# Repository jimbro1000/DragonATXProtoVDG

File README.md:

# Dragon 32 ATX Prototype VDG

This repository contains the KiCad project files
to produce the VDG component board for my
ATX Prototype backplane.

This design requires the ATX backplane board in order 
to operate
See https://github.com/jimbro1000/DragonATXProto

## Notes

Revision 1 includes a more modern RGB fed modulator
design that removes a significant problem in the 
form of the old LM1889 modulator. The board also
provides the mounting points for the various mezzanine
boards that have been previously developed. If the
mezzanine option is to be used the rest of the card
should be left unpopulated

This design has been completed using KiCad 9. Earlier
versions of KiCad are not compatible

## Theory of Operation - Video conversion

The video output of the 6847 is a form of YPrPb that
encodes the green channel data over all three of the
outputs.

To generate the RGB signal required for the AD724/725
video encoder some maths needs to be applied to
convert the YPrPb into the appropriate format.

The maths requires 5 values to be generated

Yn - the inverse signal of Y
B-Y - the inverse of Pb
Y-B - Pb
R-Y - the inverse of Pr
Y-R - Pr

Adding Yn to R-Y produces R
Adding Yn to Y-R and Y-B produces G
Adding Yn to B-Y produces B

All of the sums need weighting to make sure the results
are in some form of balance:

R = 2Yn + 2.7(R-Y)
G = 2Yn + 6.8(Y-B) + 4.7(Y-R)
B = 3Yn + 2(R-Y)

Further provision for balancing the channels is made
through a potentiometer on each channel and the result
is then normalised to provide the inputs to the AD724

## Theory of Operation - Format conversion

The 6847 video generator was designed to produce a 
video signal in NTSC format. It has no external controls
to change the format, thus in order to produce a PAL
format some cheating is required in the form of padding

The native NTSC signal is produced at a 60Hz frame rate,
while PAL requires 50Hz. In proportion the PAL video
frame has extra lines (625 vs 525), this results in near
identical lines per second between the formats (but not 
quite identical, just within tolerance).

In terms of raw refresh rate though the PAL signal 
requires an additional 100 lines of video signal are 
produced. This is achieved by suspending the video clock
for the 6847 and synthesizing 50 lines of blank video in
the upper and lower margins of the display.

This is not the end of the story though - a more fundamental
difference between NTSC and PAL is how colour information
is encoded. NTSC provides no automatic correction for any
phase errors in the signal while PAL using phase alternation
(hence the name PAL). Producing a PAL signal from NTSC 
requires the colour phase to be reversed on each consecutive
line.

The original PAL padding circuitry this replaces used a
LM1889 encoder for encoding the colour signal onto the
carrier frequency but with the AD724 and AD725 encoders
this is performed automatically.

The circuit design retains the necessary logic for
artificially producing the alternating signal but does
not utilise it.

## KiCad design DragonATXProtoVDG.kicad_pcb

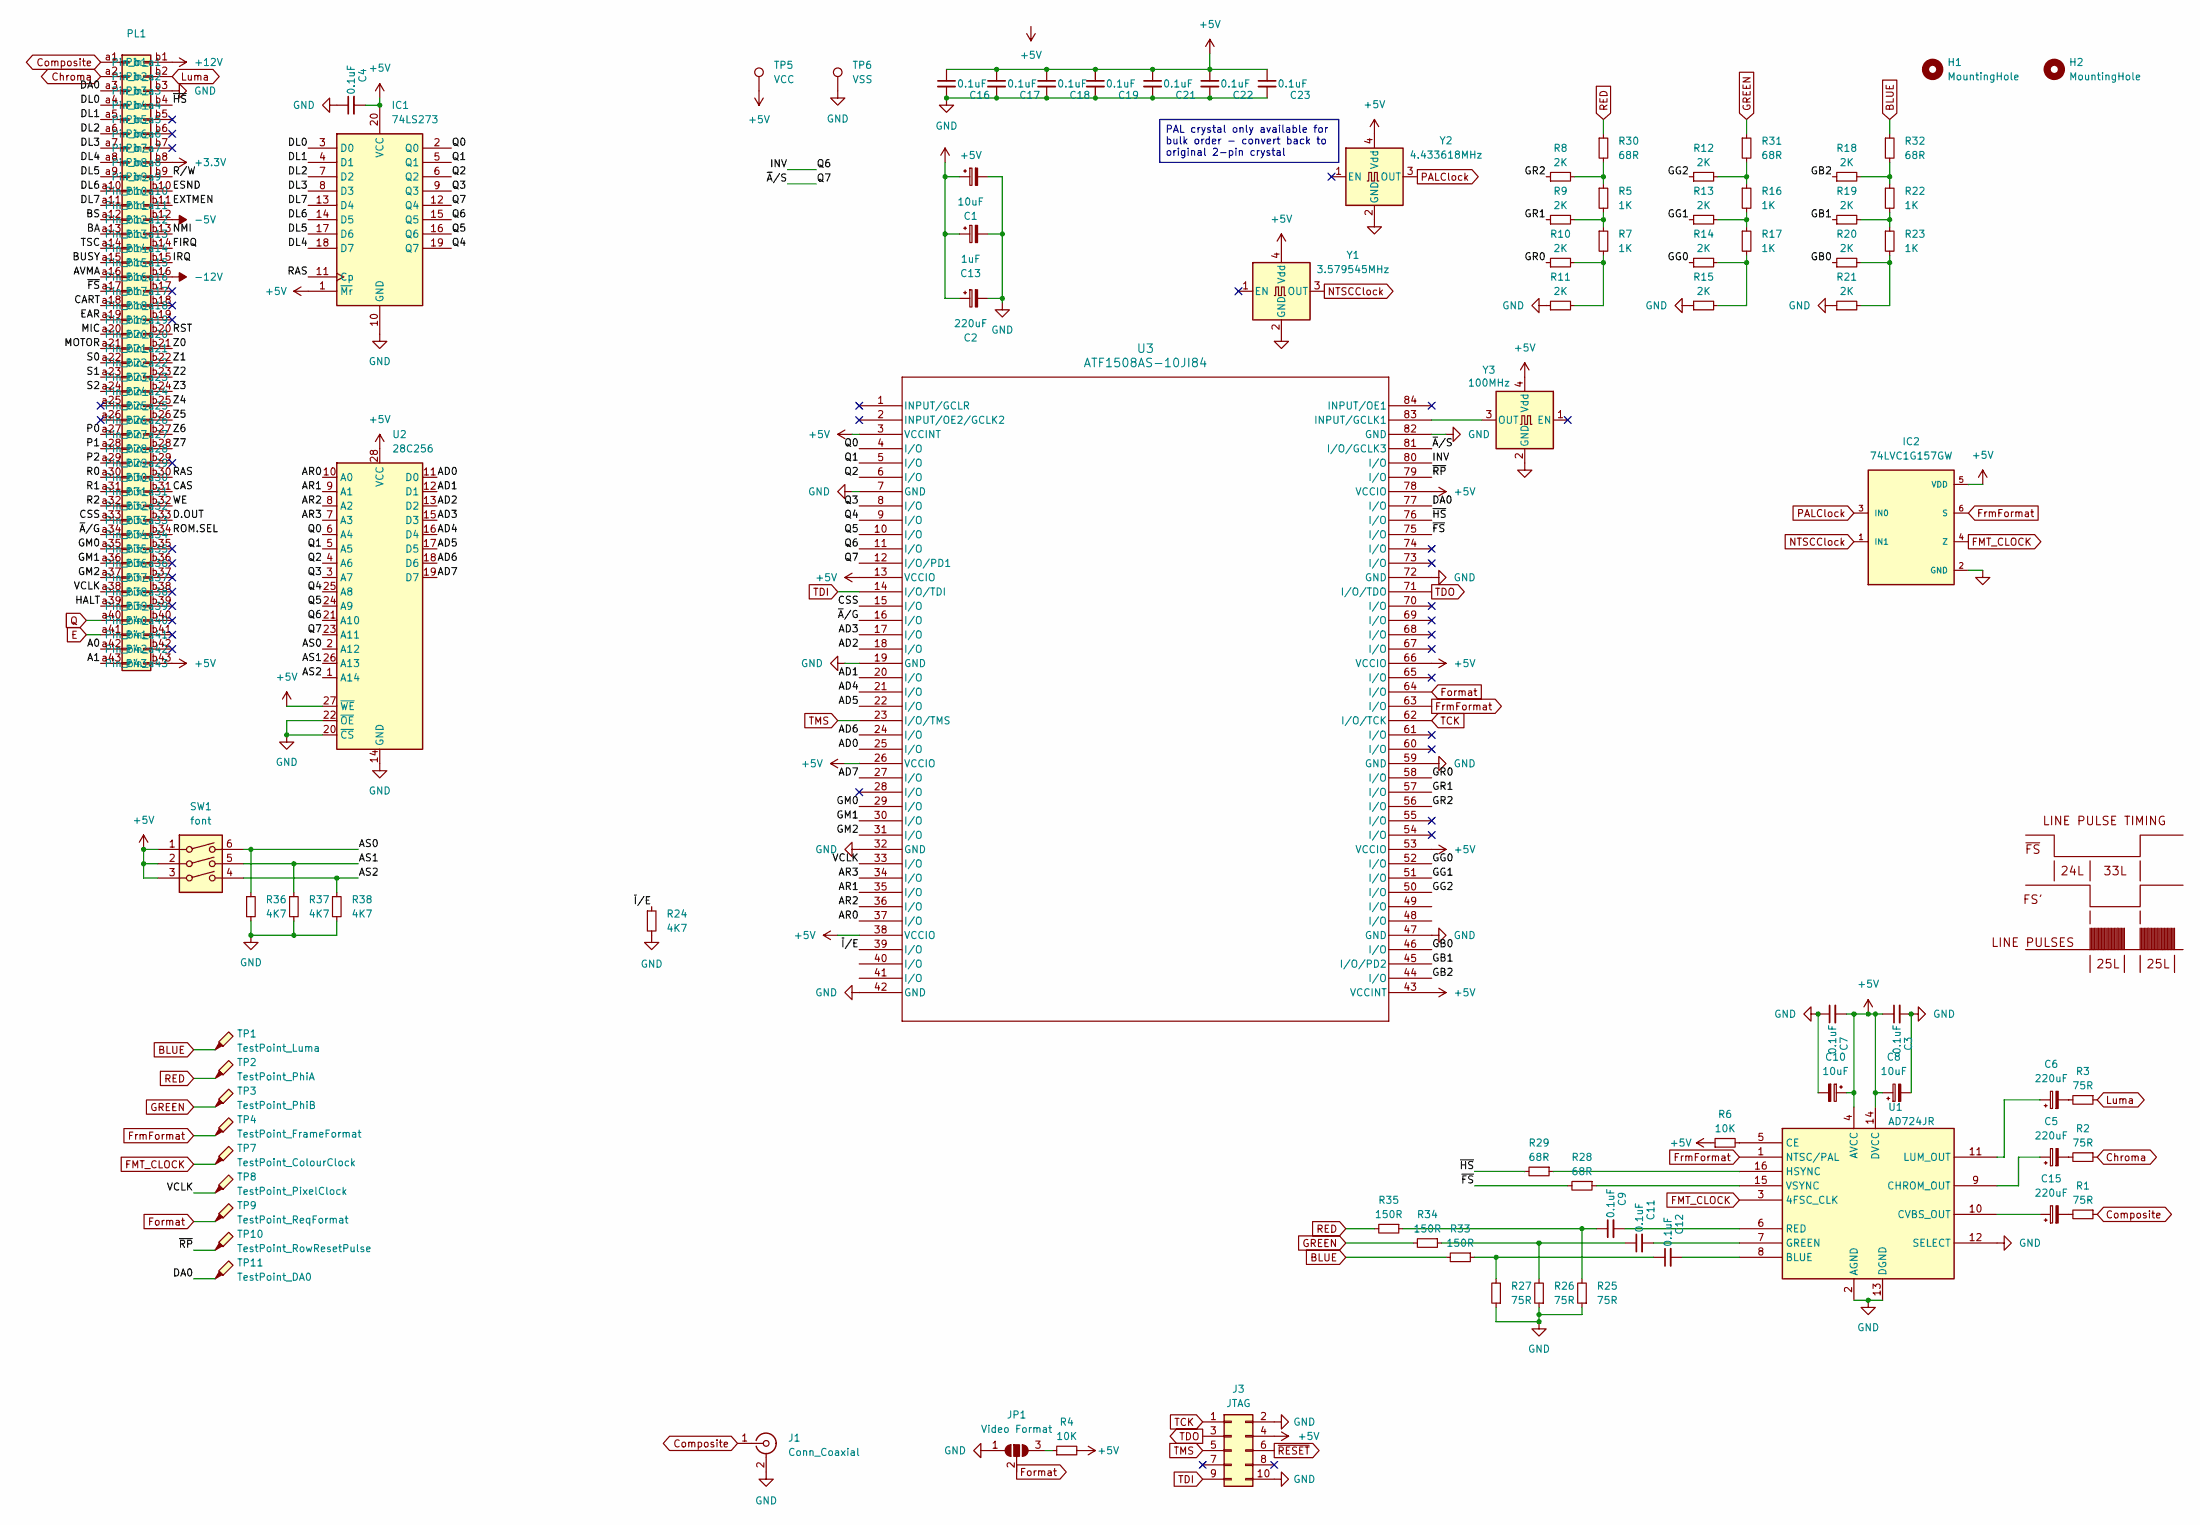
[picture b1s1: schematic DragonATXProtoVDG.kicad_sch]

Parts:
C1: 10uF; CP_Elec_4x5.4; DigiKey 732-8254-1-ND
C2: 220uF; CP_Elec_6.3x5.8; DigiKey 732-8254-1-ND
C3, C4, C7, C9, C11, C12, C16, C17, C18, C19, C21, C22, C23: 0.1uF; C_0805_2012Metric_Pad1.18x1.45mm_HandSolder; DigiKey 399-C0805C104M5RAC7800CT-ND
C5, C6, C15: 220uF; CP_EIA-6032-15_Kemet-U; DigiKey 478-1768-1-ND
C8, C10: 10uF; CP_Elec_4x5.4; DigiKey 732-6401-1-ND
C13: 1uF; CP_Elec_4x4.5; DigiKey 732-8541-1-ND
H1, H2: MountingHole; MountingHole_3.2mm_M3
IC1: 74LS273; SOIC-20W_7.5x12.8mm_P1.27mm; DigiKey 296-3682-1-ND
IC2: 74LVC1G157GW; SOT-363_SC-70-6_Handsoldering; DigiKey 1727-3491-1-ND
J1: Conn_Coaxial; Connector_RCA
J3: JTAG; PinHeader_2x05_P2.54mm_Vertical
JP1: Video Format; SolderJumper-3_P1.3mm_Open_Pad1.0x1.5mm_NumberLabels
PL1: Card_Edge_Short
R1, R2, R3: 75R; R_0805_2012Metric_Pad1.20x1.40mm_HandSolder; DigiKey CF14JT6K80CT-ND
R4, R6: 10K; R_0805_2012Metric_Pad1.20x1.40mm_HandSolder; DigiKey CF14JT6K80CT-ND
R5, R7, R16, R17, R22, R23: 1K; R_0805_2012Metric_Pad1.15x1.40mm_HandSolder
R8, R9, R10, R11, R12, R13, R14, R15, R18, R19, R20, R21: 2K; R_0805_2012Metric_Pad1.15x1.40mm_HandSolder
R24, R36, R37, R38: 4K7; R_0805_2012Metric_Pad1.15x1.40mm_HandSolder
R25, R26, R27: 75R; R_0805_2012Metric_Pad1.15x1.40mm_HandSolder
R28, R29, R30, R31, R32: 68R; R_0805_2012Metric_Pad1.15x1.40mm_HandSolder
R33, R34, R35: 150R; R_0805_2012Metric_Pad1.15x1.40mm_HandSolder
SW1: font; SW_DIP_SPSTx03_Slide_9.78x9.8mm_W7.62mm_P2.54mm
TP1: TestPoint_Luma; TestPoint_Pad_D1.0mm
TP2: TestPoint_PhiA; TestPoint_Pad_D1.0mm
TP3: TestPoint_PhiB; TestPoint_Pad_D1.0mm
TP4: TestPoint_FrameFormat; TestPoint_Pad_D1.0mm
TP5: VCC; TestPoint_Loop_D2.54mm_Drill1.5mm_Beaded
TP6: VSS; TestPoint_Loop_D2.54mm_Drill1.5mm_Beaded
TP7: TestPoint_ColourClock; TestPoint_Pad_D1.0mm
TP8: TestPoint_PixelClock; TestPoint_Pad_D1.0mm
TP9: TestPoint_ReqFormat; TestPoint_Pad_D1.0mm
TP10: TestPoint_RowResetPulse; TestPoint_Pad_D1.0mm
TP11: TestPoint_DA0; TestPoint_Pad_D1.0mm
U1: AD724JR; SOIC-16W_7.5x10.3mm_P1.27mm
U2: 28C256; DIP-28_W15.24mm
U3: ATF1508AS-10JI84; PLCC-84_THT-Socket
Y1: 3.579545MHz; Crystal_SMD_7050-4Pin_7.0x5.0mm; DigiKey XC292CT-ND
Y2: 4.433618MHz; Oscillator_SMD_SeikoEpson_SG8002LB-4Pin_5.0x3.2mm_HandSolde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; DigiKey 31-FD0440005TR-ND
Y3: 100MHz; Crystal_SMD_7050-4Pin_7.0x5.0mm; DigiKey XC327CT-ND
Z1: LINE_PULSE_DIAGRAM

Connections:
+3.3V: PL1.b8
+5V: C1.1, C2.1, C3.1, C4.2, C7.2, C8.1, C10.1, C13.1, C16.1, C17.1, C18.1, C19.1, C21.1, C22.1, C23.1, IC1.1 (~Mr), IC1.20 (VCC), IC2.5 (VDD), J3.4, PL1.b43, R4.2, R6.1, SW1.1, SW1.2, SW1.3, TP5.1, U1.4 (AVCC), U1.14 (DVCC), U2.27 (~WE), U2.28 (VCC), U3.3 (VCCINT), U3.13 (VCCIO), U3.26 (VCCIO), U3.38 (VCCIO), U3.43 (VCCINT), U3.53 (VCCIO), U3.66 (VCCIO), U3.78 (VCCIO), Y1.4 (Vdd), Y2.4 (Vdd), Y3.4 (Vdd)
+12V: PL1.b1
-5V: PL1.b12
-12V: PL1.b16
/A0: PL1.a42
/A1: PL1.a43
/AD0: U2.11 (D0), U3.25 (I/O)
/AD1: U2.12 (D1), U3.20 (I/O)
/AD2: U2.13 (D2), U3.18 (I/O)
/AD3: U2.15 (D3), U3.17 (I/O)
/AD4: U2.16 (D4), U3.21 (I/O)
/AD5: U2.17 (D5), U3.22 (I/O)
/AD6: U2.18 (D6), U3.24 (I/O)
/AD7: U2.19 (D7), U3.27 (I/O)
/AR0: U2.10 (A0), U3.37 (I/O)
/AR1: U2.9 (A1), U3.35 (I/O)
/AR2: U2.8 (A2), U3.36 (I/O)
/AR3: U2.7 (A3), U3.34 (I/O)
/AS0: R36.1, SW1.6, U2.2 (A12)
/AS1: R37.1, SW1.5, U2.26 (A13)
/AS2: R38.1, SW1.4, U2.1 (A14)
/AVMA: PL1.a16
/BA: PL1.a13
/BS: PL1.a12
/BUSY: PL1.a15
/CART: PL1.a18
/CAS: PL1.b31
/CSS: PL1.a33, U3.15 (I/O)
/D.OUT: PL1.b33
/DA0: PL1.a3, TP11.1, U3.77 (I/O)
/DL0: IC1.3 (D0), PL1.a4
/DL1: IC1.4 (D1), PL1.a5
/DL2: IC1.7 (D2), PL1.a6
/DL3: IC1.8 (D3), PL1.a7
/DL4: IC1.18 (D7), PL1.a8
/DL5: IC1.17 (D6), PL1.a9
/DL6: IC1.14 (D5), PL1.a10
/DL7: IC1.13 (D4), PL1.a11
/EAR: PL1.a19
/ESND: PL1.b10
/EXTMEN: PL1.b11
/FIRQ: PL1.b14
/GB0: R20.1, U3.46 (I/O)
/GB1: R19.1, U3.45 (I/O/PD2)
/GB2: R18.1, U3.44 (I/O)
/GG0: R14.1, U3.52 (I/O)
/GG1: R13.1, U3.51 (I/O)
/GG2: R12.1, U3.50 (I/O)
/GM0: PL1.a35, U3.29 (I/O)
/GM1: PL1.a36, U3.30 (I/O)
/GM2: PL1.a37, U3.31 (I/O)
/GR0: R10.1, U3.58 (I/O)
/GR1: R9.1, U3.57 (I/O)
/GR2: R8.1, U3.56 (I/O)
/HALT: PL1.a39
/INV: IC1.15 (Q5), U2.21 (A10), U3.11 (I/O), U3.80 (I/O)
/IRQ: PL1.b15
/MIC: PL1.a20
/MOTOR: PL1.a21
/NMI: PL1.b13
/P0: PL1.a27
/P1: PL1.a28
/P2: PL1.a29
/Q0: IC1.2 (Q0), U2.6 (A4), U3.4 (I/O)
/Q1: IC1.5 (Q1), U2.5 (A5), U3.5 (I/O)
/Q2: IC1.6 (Q2), U2.4 (A6), U3.6 (I/O)
/Q3: IC1.9 (Q3), U2.3 (A7), U3.8 (I/O)
/Q4: IC1.19 (Q7), U2.25 (A8), U3.9 (I/O)
/Q5: IC1.16 (Q6), U2.24 (A9), U3.10 (I/O)
/Q7: IC1.12 (Q4), U2.23 (A11), U3.12 (I/O/PD1), U3.81 (I/O/GCLK3)
/R0: PL1.a30
/R1: PL1.a31
/R2: PL1.a32
/RAS: IC1.11 (Cp), PL1.b30
/ROM.SEL: PL1.b34
/RST: PL1.b20
/R/W: PL1.b9
/S0: PL1.a22
/S1: PL1.a23
/S2: PL1.a24
/TSC: PL1.a14
/VCLK: PL1.a38, TP8.1, U3.33 (I/O)
/WE: PL1.b32
/Z0: PL1.b21
/Z1: PL1.b22
/Z2: PL1.b23
/Z3: PL1.b24
/Z4: PL1.b25
/Z5: PL1.b26
/Z6: PL1.b27
/Z7: PL1.b28
/~A/G: PL1.a34, U3.16 (I/O)
/~FS: PL1.a17, R28.2, U3.75 (I/O)
/~HS: PL1.b4, R29.2, U3.76 (I/O)
/~I/E: R24.1, U3.39 (I/O)
/~RP: TP10.1, U3.79 (I/O)
BLUE: R32.1, R33.2, TP1.1
Chroma: PL1.a2, R2.1
Composite: J1.1 (In), PL1.a1, R1.1
E: PL1.a41
FMT_CLOCK: IC2.4 (Z), TP7.1, U1.3 (4FSC_CLK)
Format: JP1.2 (C), TP9.1, U3.64 (I/O)
FrmFormat: IC2.6 (S), TP4.1, U1.1 (NTSC/PAL), U3.63 (I/O)
GND: C1.2, C2.2, C3.2, C4.1, C7.1, C8.2, C10.2, C13.2, C16.2, C17.2, C18.2, C19.2, C21.2, C22.2, C23.2, IC1.10 (GND), IC2.2 (GND), J1.2 (Ext), J3.2, J3.10, JP1.1 (A), PL1.b3, R11.1, R15.1, R21.1, R24.2, R25.1, R26.1, R27.1, R36.2, R37.2, R38.2, TP6.1, U1.2 (AGND), U1.12 (SELECT), U1.13 (DGND), U2.14 (GND), U2.20 (~CS), U2.22 (~OE), U3.7 (GND), U3.19 (GND), U3.32 (GND), U3.42 (GND), U3.47 (GND), U3.59 (GND), U3.72 (GND), U3.82 (GND), Y1.2 (GND), Y2.2 (GND), Y3.2 (GND)
GREEN: R31.1, R34.2, TP3.1
Luma: PL1.b2, R3.1
NTSCClock: IC2.1 (IN1), Y1.3 (OUT)
unnamed: C5.2, R2.2
unnamed: C6.2, R3.2
unnamed: C9.1, R25.2, R35.1
unnamed: C11.1, R26.2, R34.1
unnamed: C12.1, R27.2, R33.1
unnamed: C15.2, R1.2
unnamed: JP1.3 (B), R4.1
unnamed: R5.2, R7.1, R9.2
unnamed: R7.2, R10.2, R11.2
unnamed: R12.2, R16.1, R31.2
unnamed: R13.2, R16.2, R17.1
unnamed: R14.2, R15.2, R17.2
unnamed: R18.2, R22.1, R32.2
unnamed: R19.2, R22.2, R23.1
unnamed: R20.2, R21.2, R23.2
unnamed: R5.1, R8.2, R30.2
unnamed: C12.2, U1.8 (BLUE)
unnamed: R6.2, U1.5 (CE)
unnamed: C5.1, U1.9 (CHROM_OUT)
unnamed: C15.1, U1.10 (CVBS_OUT)
unnamed: C11.2, U1.7 (GREEN)
unnamed: R29.1, U1.16 (HSYNC)
unnamed: C6.1, U1.11 (LUM_OUT)
unnamed: C9.2, U1.6 (RED)
unnamed: R28.1, U1.15 (VSYNC)
unnamed: U3.83 (INPUT/GCLK1), Y3.3 (OUT)
PALClock: IC2.3 (IN0), Y2.3 (OUT)
Q: PL1.a40
RED: R30.1, R35.2, TP2.1
TCK: J3.1, U3.62 (I/O/TCK)
TDI: J3.9, U3.14 (I/O/TDI)
TDO: J3.3, U3.71 (I/O/TDO)
TMS: J3.5, U3.23 (I/O/TMS)
~RESET: J3.6

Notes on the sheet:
PAL crystal only available for bulk order - convert back to original 2-pin crystal

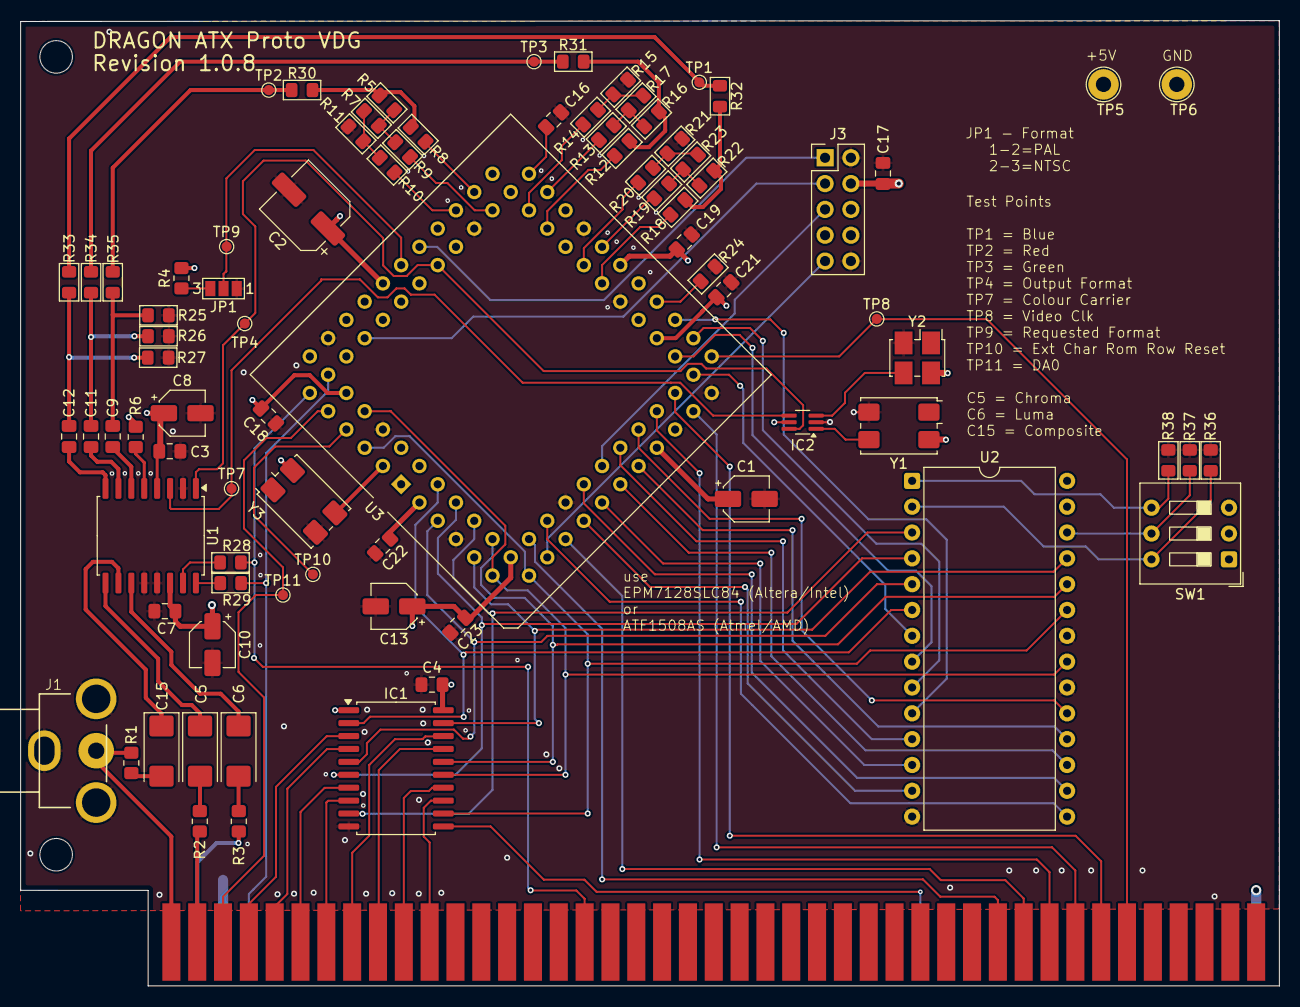
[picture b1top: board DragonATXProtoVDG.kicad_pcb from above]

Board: 4 copper layers, 123.8 x 94.9 mm, 85 parts (0 on the bottom side), 95 nets.

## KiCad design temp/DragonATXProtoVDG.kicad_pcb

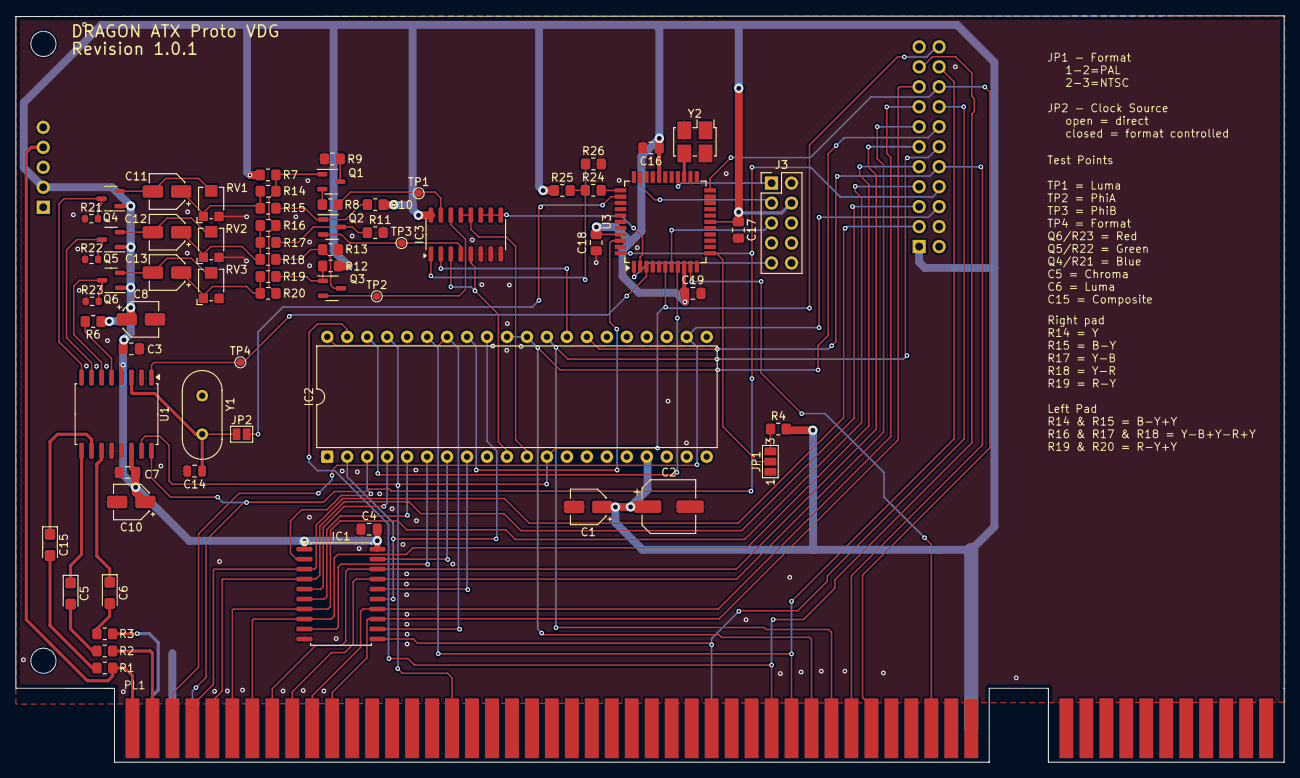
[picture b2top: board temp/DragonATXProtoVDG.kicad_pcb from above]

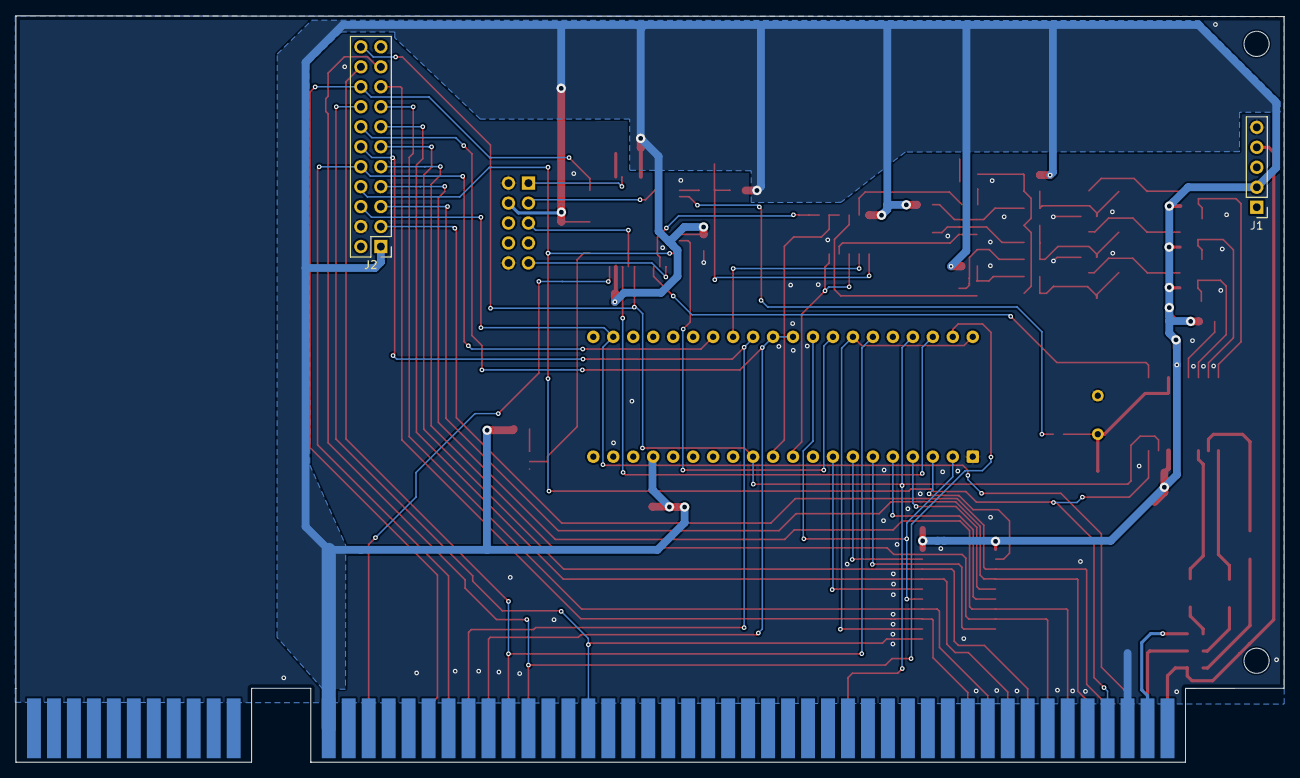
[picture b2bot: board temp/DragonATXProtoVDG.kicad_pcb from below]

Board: 2 copper layers, 161.3 x 94.9 mm, 71 parts (2 on the bottom side), 76 nets.

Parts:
C1, C8, C10, C11, C12, C13: 10uF; CP_Elec_4x5.4
C2: 100uF; CP_Elec_6.3x5.8
C3, C4, C7, C16, C17, C18, C19: 0.1uF; C_0805_2012Metric_Pad1.18x1.45mm_HandSolder
C5, C6, C15: 220uF; CP_EIA-3216-12_Kemet-S
C14: 51pF; C_0805_2012Metric
H1, H2: MountingHole; MountingHole_3.2mm_M3
IC1: 74LS273; SOIC-20W_7.5x12.8mm_P1.27mm
IC2: MC6847; DIP-40_W15.24mm
IC3: MC14053; SOIC-16_3.9x9.9mm_P1.27mm
J1: Video Output; PinHeader_1x05_P2.54mm_Vertical
J2: Board Interconnect Male; PinHeader_2x11_P2.54mm_Vertical
J3: JTAG; PinHeader_2x05_P2.54mm_Vertical
JP1: Video Format; SolderJumper-3_P1.3mm_Open_Pad1.0x1.5mm_NumberLabels
JP2: FormatClock; SolderJumper-2_P1.3mm_Open_Pad1.0x1.5mm
PL1: Card_Edge
Q1: MMBT4401; SOT-23-3
Q2, Q3, Q4, Q5, Q6: NPN; SOT-23-3
R1, R2, R3: 75R; R_0805_2012Metric_Pad1.20x1.40mm_HandSolder
R4, R6: 10K; R_0805_2012Metric_Pad1.20x1.40mm_HandSolder
R7: 180R; R_0805_2012Metric_Pad1.20x1.40mm_HandSolder
R8: 910R; R_0805_2012Metric_Pad1.20x1.40mm_HandSolder
R9: 100R; R_0805_2012Metric_Pad1.20x1.40mm_HandSolder
R10, R11, R12, R13: 150R; R_0805_2012Metric_Pad1.20x1.40mm_HandSolder
R14: 3K3; R_0805_2012Metric_Pad1.20x1.40mm_HandSolder
R15: 2K2; R_0805_2012Metric_Pad1.20x1.40mm_HandSolder
R16, R20: 2K; R_0805_2012Metric_Pad1.20x1.40mm_HandSolder
R17: 6K8; R_0805_2012Metric_Pad1.20x1.40mm_HandSolder
R18: 4K7; R_0805_2012Metric_Pad1.20x1.40mm_HandSolder
R19: 2K7; R_0805_2012Metric_Pad1.20x1.40mm_HandSolder
R21, R22, R23: 150R; R_0603_1608Metric
R24: 12K; R_0805_2012Metric_Pad1.20x1.40mm_HandSolder
R25: 8K2; R_0805_2012Metric_Pad1.20x1.40mm_HandSolder
R26: 1K8; R_0805_2012Metric_Pad1.20x1.40mm_HandSolder
RV1, RV2, RV3: 50K; Potentiometer_Bourns_TC33X_Vertical
TP1: TestPoint_Luma; TestPoint_Pad_D1.0mm
TP2: TestPoint_PhiA; TestPoint_Pad_D1.0mm
TP3: TestPoint_PhiB; TestPoint_Pad_D1.0mm
TP4: TestPoint_FrameFormat; TestPoint_Pad_D1.0mm
U1: AD724JR; SOIC-16W_7.5x10.3mm_P1.27mm
U3: ATF1502ASL-xAx44; TQFP-44_10x10mm_P0.8mm
Y1: 4.433620MHz; Crystal_HC18-U_Vertical
Y2: 4.433618MHz; Oscillator_SMD_SeikoEpson_SG8002LB-4Pin_5.0x3.2mm_HandSolde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

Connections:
+5V: C1.1, C2.1, C3.1, C4.2, C7.2, C8.1, C10.1, C16.1, C17.1, C18.1, C19.1, IC1.1 (~Mr), IC1.20 (VCC), IC2.17 (VCC), IC3.16 (VDD), J1.2, J2.1, J3.4, PL1.b43, Q4.1 (C), Q5.1 (C), Q6.1 (C), R4.2, R6.1, R7.2, R10.2, R12.2, R25.1, U1.4 (AVCC), U1.14 (DVCC), U3.9 (VCC), U3.17 (VCC), U3.29 (VCC), U3.41 (VCC)
/B-Y: Q2.1 (C), R10.1, R15.2
/CSS: IC2.39 (CSS), J2.19, PL1.a33
/DA0: IC2.22 (DA0), J2.6, PL1.a3
/DL0: IC1.3 (D0), J2.3, PL1.a4
/DL1: IC1.4 (D1), J2.5, PL1.a5
/DL2: IC1.7 (D2), J2.7, PL1.a6
/DL3: IC1.8 (D3), J2.9, PL1.a7
/DL4: IC1.18 (D7), J2.11, PL1.a8
/DL5: IC1.17 (D6), J2.13, PL1.a9
/DL6: IC1.14 (D5), J2.15, PL1.a10
/DL7: IC1.13 (D4), J2.17, PL1.a11
/GM0: IC2.30 (GM0), IC2.31 (~INT/EXT), J2.14, PL1.a35
/GM1: IC2.29 (GM1), J2.12, PL1.a36
/GM2: IC2.27 (GM2), J2.10, PL1.a37
/HS: J2.8, PL1.b4, U1.16 (HSYNC), U3.44 (I/O)
/Q0: IC1.2 (Q0), IC2.3 (D0)
/Q1: IC1.5 (Q1), IC2.4 (D1)
/Q2: IC1.6 (Q2), IC2.5 (D2)
/Q3: IC1.9 (Q3), IC2.6 (D3)
/Q4: IC1.19 (Q7), IC2.7 (D4)
/Q5: IC1.16 (Q6), IC2.8 (D5)
/Q6: IC1.15 (Q5), IC2.2 (D6), IC2.32 (INV)
/Q7: IC1.12 (Q4), IC2.34 (~A/S), IC2.40 (D7)
/R-Y: Q3.1 (C), R12.1, R19.2
/RAS: IC1.11 (Cp), J2.16, PL1.b30
/VCLK: J2.18, PL1.a38, U3.22 (I/O)
/Y-B: Q2.3 (E), R11.2, R17.2
/Y-R: Q3.3 (E), R13.2, R18.2
/~A/G: IC2.35 (~A/G), J2.20, PL1.a34
/~Y: Q1.1 (C), R7.1, R14.2, R16.2, R20.2
BLUE: Q4.3 (E), R21.2, U1.8 (BLUE)
CLK: IC2.33 (CLK), U3.42 (I/O)
Chroma: PL1.a2, R2.1
Composite: J1.4, PL1.a1, R1.1
E: PL1.a41, U3.10 (I/O)
FMT_CLOCK: JP2.2 (B), U3.35 (I/O/GCLK3)
Format: JP1.2 (C), U3.12 (I/O)
FrmFormat: TP4.1, U1.1 (NTSC/PAL), U3.3 (I/O)
GND: C1.2, C2.2, C3.2, C4.1, C7.1, C8.2, C10.2, C14.2, C16.2, C17.2, C18.2, C19.2, IC1.10 (GND), IC2.1 (GND), IC3.6 (INHIBIT), IC3.7 (VEE), IC3.8 (VSS), J1.5, J2.4, J3.2, J3.10, JP1.1 (A), PL1.b3, R9.1, R11.1, R13.1, R21.1, R22.1, R23.1, R26.2, RV1.3, RV2.3, RV3.3, U1.2 (AGND), U1.12 (SELECT), U1.13 (DGND), U3.4 (GND), U3.16 (GND), U3.24 (GND), U3.36 (GND), Y1.1, Y2.2 (GND), Y2.4 (Vdd)
GREEN: Q5.3 (E), R22.2, U1.7 (GREEN)
LUM: IC2.28 (Y), IC3.2 (Y0)
LUM CONTROL: IC3.9 (C), IC3.10 (B), IC3.11 (A), U3.2 (I/O)
LUM': IC3.15 (Y), R8.2, TP1.1
Luma: PL1.b2, R3.1
unnamed: C5.2, R2.2
unnamed: C6.2, R3.2
unnamed: C11.1, R14.1, R15.1, RV1.1
unnamed: C12.1, R16.1, R17.1, R18.1, RV2.1
unnamed: C13.1, R19.1, R20.1, RV3.1
unnamed: C15.2, R1.2
unnamed: JP1.3 (B), R4.1
unnamed: C14.1, JP2.1 (A), U1.3 (4FSC_CLK), Y1.2
unnamed: Q1.2 (B), R8.1
unnamed: Q1.3 (E), R9.2
unnamed: C11.2, Q4.2 (B), RV1.2
unnamed: C12.2, Q5.2 (B), RV2.2
unnamed: C13.2, Q6.2 (B), RV3.2
unnamed: R24.2, U3.34 (I/O)
unnamed: R6.2, U1.5 (CE)
unnamed: C5.1, U1.9 (CHROM_OUT)
unnamed: C15.1, U1.10 (CVBS_OUT)
unnamed: C6.1, U1.11 (LUM_OUT)
PALClock: U3.25 (I/O), Y2.3 (OUT)
PadLuma: IC3.1 (Y1), R24.1, R25.2, R26.1
RED: Q6.3 (E), R23.2, U1.6 (RED)
TCK: J3.1, U3.26 (I/O/TCK)
TDI: J3.9, U3.1 (I/O/TDI)
TDO: J3.3, U3.32 (I/O/TDO)
TMS: J3.5, U3.7 (I/O/TMS)
phiA: IC2.11 (A), IC3.12 (X0), IC3.13 (X1)
phiA': IC3.14 (X), Q3.2 (B), TP2.1
phiB: IC2.10 (B), IC3.3 (Z1), IC3.5 (Z0)
phiB': IC3.4 (Z), Q2.2 (B), TP3.1
~FS: IC2.12 (~MS), IC2.37 (~FS), J2.22, PL1.a17, U1.15 (VSYNC), U3.6 (I/O)
~HS: IC2.38 (~HS), U3.8 (I/O)

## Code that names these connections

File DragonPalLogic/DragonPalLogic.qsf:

# -------------------------------------------------------------------------- #
#
# Copyright (C) 1991-2013 Altera Corporation
# Your use of Altera Corporation's design tools, logic functions 
# and other software and tools, and its AMPP partner logic 
# functions, and any output files from any of the foregoing 
# (including device programming or simulation files), and any 
# associated documentation or information are expressly subject 
# to the terms and conditions of the Altera Program License 
# Subscription Agreement, Altera MegaCore Function License 
# Agreement, or other applicable license agreement, including, 
# without limitation, that your use is for the sole purpose of 
# programming logic devices manufactured by Altera and sold by 
# Altera or its authorized distributors.  Please refer to the 
# applicable agreement for further details.
#
# -------------------------------------------------------------------------- #
#
# Quartus II 64-Bit
# Version 13.0.1 Build 232 06/12/2013 Service Pack 1 SJ Web Edition
# Date created = 18:42:37  June 02, 2025
#
# -------------------------------------------------------------------------- #
#
# Notes:
#
# 1) The default values for assignments are stored in the file:
#		DragonPalLogic_assignment_defaults.qdf
#    If this file doesn't exist, see file:
#		assignment_defaults.qdf
#
# 2) Altera recommends that you do not modify this file. This
#    file is updated automatically by the Quartus II software
#    and any changes you make may be lost or overwritten.
#
# -------------------------------------------------------------------------- #


set_global_assignment -name FAMILY MAX7000AE
set_global_assignment -name DEVICE "EPM7064AETC44-10"
set_global_assignment -name TOP_LEVEL_ENTITY DragonPalLogic
set_global_assignment -name ORIGINAL_QUARTUS_VERSION "13.0 SP1"
set_global_assignment -name PROJECT_CREATION_TIME_DATE "18:42:37  JUNE 02, 2025"
set_global_assignment -name LAST_QUARTUS_VERSION "13.0 SP1"
set_global_assignment -name VERILOG_FILE VClkPulseGenerator.v -hdl_version Verilog_2001
set_global_assignment -name VERILOG_FILE VClkInterposer.v -hdl_version Verilog_2001
set_global_assignment -name VERILOG_FILE HSnCounter.v -hdl_version Verilog_2001
set_global_assignment -name VERILOG_FILE DecaQuintCounter.v -hdl_version Verilog_2001
set_global_assignment -name PROJECT_OUTPUT_DIRECTORY output_files
set_global_assignment -name ERROR_CHECK_FREQUENCY_DIVISOR "-1"
set_global_assignment -name EDA_DESIGN_ENTRY_SYNTHESIS_TOOL "Design Compiler"
set_global_assignment -name EDA_INPUT_VCC_NAME VDD -section_id eda_design_synthesis
set_global_assignment -name EDA_LMF_FILE altsyn.lmf -section_id eda_design_synthesis
set_global_assignment -name EDA_INPUT_DATA_FORMAT EDIF -section_id eda_design_synthesis
set_global_assignment -name EDA_SIMULATION_TOOL "ModelSim (Verilog)"
set_global_assignment -name EDA_TIME_SCALE "1 ps" -section_id eda_simulation
set_global_assignment -name EDA_OUTPUT_DATA_FORMAT "VERILOG HDL" -section_id eda_simulation
set_global_assignment -name EDA_BOARD_DESIGN_TIMING_TOOL "Stamp (Timing)"
set_global_assignment -name EDA_OUTPUT_DATA_FORMAT STAMP -section_id eda_board_design_timing
set_global_assignment -name EDA_BOARD_DESIGN_SYMBOL_TOOL "ViewDraw (Symbol)"
set_global_assignment -name EDA_OUTPUT_DATA_FORMAT VIEWDRAW -section_id eda_board_design_symbol
set_global_assignment -name EDA_BOARD_DESIGN_SIGNAL_INTEGRITY_TOOL "<None>"
set_global_assignment -name EDA_OUTPUT_DATA_FORMAT NONE -section_id eda_board_design_signal_integrity
set_global_assignment -name EDA_BOARD_DESIGN_BOUNDARY_SCAN_TOOL "<None>"
set_global_assignment -name EDA_OUTPUT_DATA_FORMAT NONE -section_id eda_board_design_boundary_scan
set_global_assignment -name VERILOG_FILE DragonPalLogic.v
set_global_assignment -name OPTIMIZE_HOLD_TIMING OFF
set_global_assignment -name OPTIMIZE_MULTI_CORNER_TIMING OFF
set_global_assignment -name FITTER_EFFORT "STANDARD FIT"
set_global_assignment -name MAX7000_DEVICE_IO_STANDARD "3.3-V LVTTL"
set_location_assignment PIN_2 -to LUMA_CONTROL
set_location_assignment PIN_3 -to FrmFormat
set_location_assignment PIN_6 -to FSn
set_location_assignment PIN_8 -to HSn
set_location_assignment PIN_12 -to Format
set_location_assignment PIN_22 -to VClk
set_location_assignment PIN_25 -to PALClock
set_location_assignment PIN_44 -to HS
set_location_assignment PIN_42 -to CLK
set_location_assignment PIN_35 -to FormatClock
set_location_assignment PIN_30 -to LINE_PULSE
set_location_assignment PIN_34 -to PAD_LUMA
set_global_assignment -name SDC_FILE DragonPalLogic.sdc
set_instance_assignment -name IO_STANDARD TTL -to LUMA_CONTROL
set_instance_assignment -name IO_STANDARD TTL -to FrmFormat
set_instance_assignment -name IO_STANDARD TTL -to FSn
set_instance_assignment -name IO_STANDARD TTL -to HSn
set_instance_assignment -name IO_STANDARD TTL -to Format
set_instance_assignment -name IO_STANDARD TTL -to VClk
set_instance_assignment -name IO_STANDARD TTL -to PALClock
set_instance_assignment -name IO_STANDARD TTL -to LINE_PULSE
set_instance_assignment -name IO_STANDARD TTL -to PAD_LUMA
set_instance_assignment -name IO_STANDARD TTL -to FormatClock
set_instance_assignment -name IO_STANDARD TTL -to CLK
set_instance_assignment -name IO_STANDARD TTL -to HS

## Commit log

2025-03-19 upgrade card edge spec
2025-03-24 prepare for fabrication
2025-06-02 refine design for ATF1504
2025-06-02 include verilog code for ATF1504
2025-06-03 update board render
2025-06-03 rework for path gates
2025-06-03 Update README.md
    Fix end of line whitespace
2025-06-03 Update README.md
    Correction to RGB equations
2025-06-04 swap to larger CPLD
2025-06-04 revert accidental changes
2025-06-05 switch to PLCC
2025-06-06 resolve routing
2025-06-28 rework layout
2025-06-28 revise cpld logic
2025-07-18 update CPLD
2025-07-18 include full VDG replacement code
2025-07-23 fix luma attenuation
2025-07-30 convert to use lhm1251
2025-11-09 refine board design
2025-11-19 refresh
2026-01-03 revise for 1.0.7
2026-01-03 condition rgb
2026-01-04 regenerate PCB render
2026-01-24 redesign for character rom
2026-01-28 rewire
